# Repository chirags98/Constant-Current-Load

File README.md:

# Constant-Current-Load

This circuit uses an opamp and a mosfet as a voltage follower circuit. I can dial in any current I want and the circuit will adjust itself to draw that much current from the power supply regardless of the supply voltage. It can be 3 Volts, 5 Volts, 15 Volts whatever it might be and the load will adjust itself to draw the selected current.

This is a double sided board design which I got manufactured from a PCB prototyping firm in China.

I designed the circuit to have the following features

* To have a knob to vary the current from 1mA-2A
* Dissipate upto 30 watts of power
* Connect a supply upto 30 volts
* To have a LCD panel to show 
    * Current drawn
    * Voltage across the load
    * Power dissipated in the load
* Give warnings if power/current/voltage range are excedded
* Give the user the choice to run the circuit from the load supply thereby eliminating the need for an external power supply

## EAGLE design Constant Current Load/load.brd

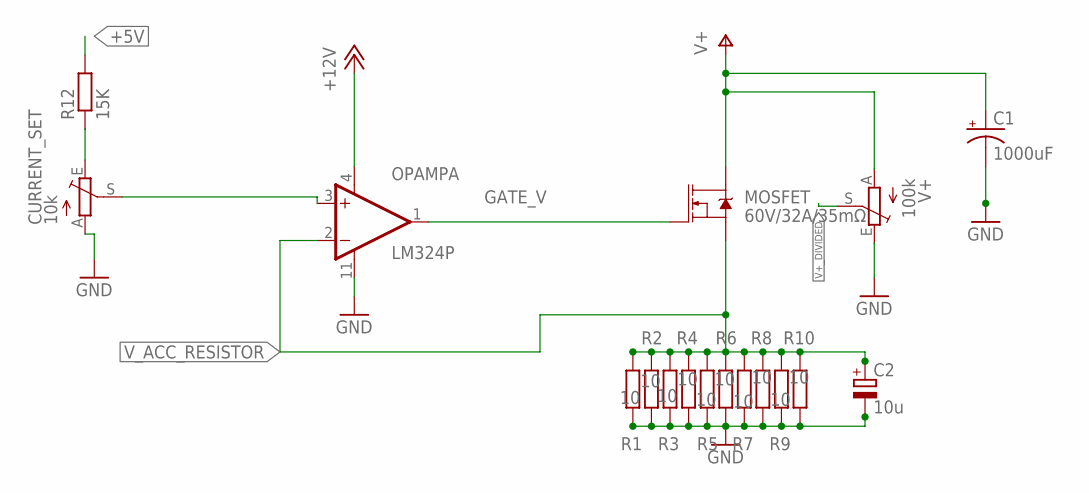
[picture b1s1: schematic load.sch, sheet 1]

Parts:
C1: 1000uF; CPOL-RADIAL-5MM-10MM
C2: 10u; E2,5-6E
CURRENT_SET: 10k; S64W
MOSFET: 60V/32A/35mΩ; TO220V
OPAMP: LM324P; DIL14
R1, R2, R3, R4, R5, R6, R7, R8, R9, R10: 10; 0207/12
R12: 15K; M0805
V+: 100k; S64W

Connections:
+5V: R12.2; also elsewhere on the board
+12V: OPAMP.4 (V+); also elsewhere on the board
GATE_V: MOSFET.1 (G), OPAMP.1 (OUT); also elsewhere on the board
GND: C1.-, C2.-, CURRENT_SET.A, OPAMP.11 (V-), R1.1, R2.1, R3.1, R4.1, R5.1, R6.1, R7.1, R8.1, R9.1, R10.1, V+.E; also elsewhere on the board
unnamed: CURRENT_SET.S, OPAMP.3 (+IN)
unnamed: CURRENT_SET.E, R12.1
V+: C1.+, MOSFET.2 (D), V+.A; also elsewhere on the board
V+_DIVIDED: V+.S; also elsewhere on the board
V_ACC_RESISTOR: C2.+, MOSFET.3 (S), OPAMP.2 (-IN), R1.2, R2.2, R3.2, R4.2, R5.2, R6.2, R7.2, R8.2, R9.2, R10.2; also elsewhere on the board

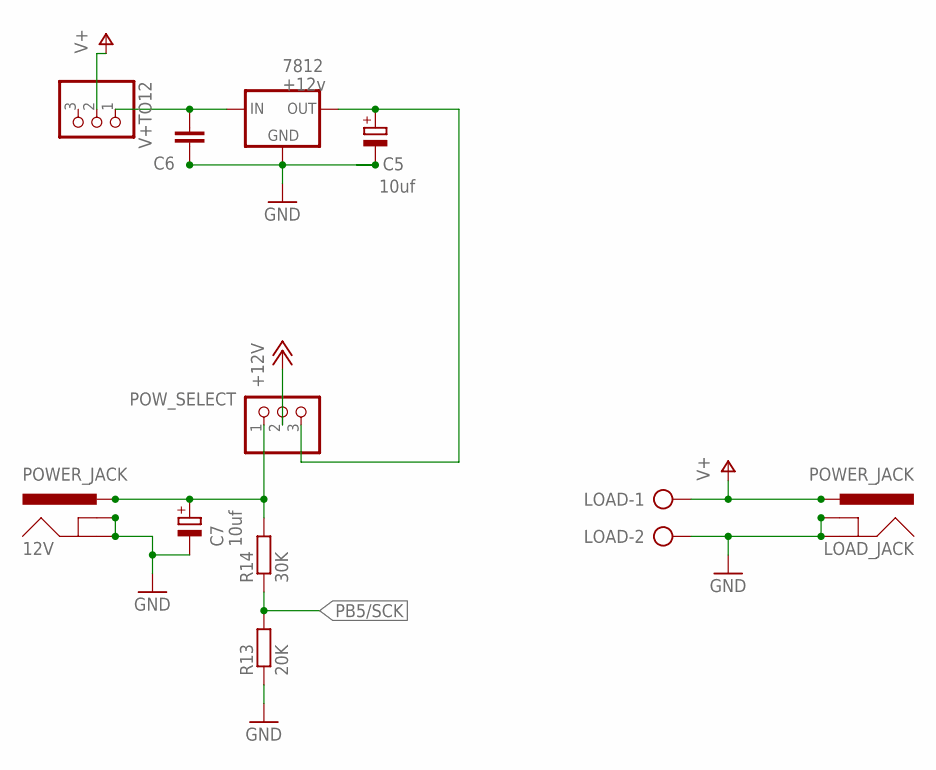
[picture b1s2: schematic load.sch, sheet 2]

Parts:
12V: POWER_JACK; POWER_JACK_PTH
7812: +12v; TO-252
C5, C7: 10uf; E2,5-6
C6: .1uF; C0805K
LOAD: AK500/2-H
LOAD_JACK: POWER_JACK; POWER_JACK_PTH
POW_SELECT: PINHD-1X3; 1X03
R13: 20K; M0805
R14: 30K; M0805
V+TO12: PINHD-1X3; 1X03

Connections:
12V_JACK_INPUT: 12V.PWR, C7.+, POW_SELECT.1, R14.2
12V_REG_O/P: 7812.2 (OUT), C5.+, POW_SELECT.3
+12V: POW_SELECT.2; also elsewhere on the board
GND: 12V.GND, 12V.GNDBREAK, 7812.3 (GND), C5.-, C6.2, C7.-, LOAD.2, LOAD_JACK.GND, LOAD_JACK.GNDBREAK, R13.1; also elsewhere on the board
unnamed: 7812.1 (IN), C6.1, V+TO12.1
PB5/SCK: R13.2, R14.1; also elsewhere on the board
V+: LOAD.1, LOAD_JACK.PWR, V+TO12.2; also elsewhere on the board

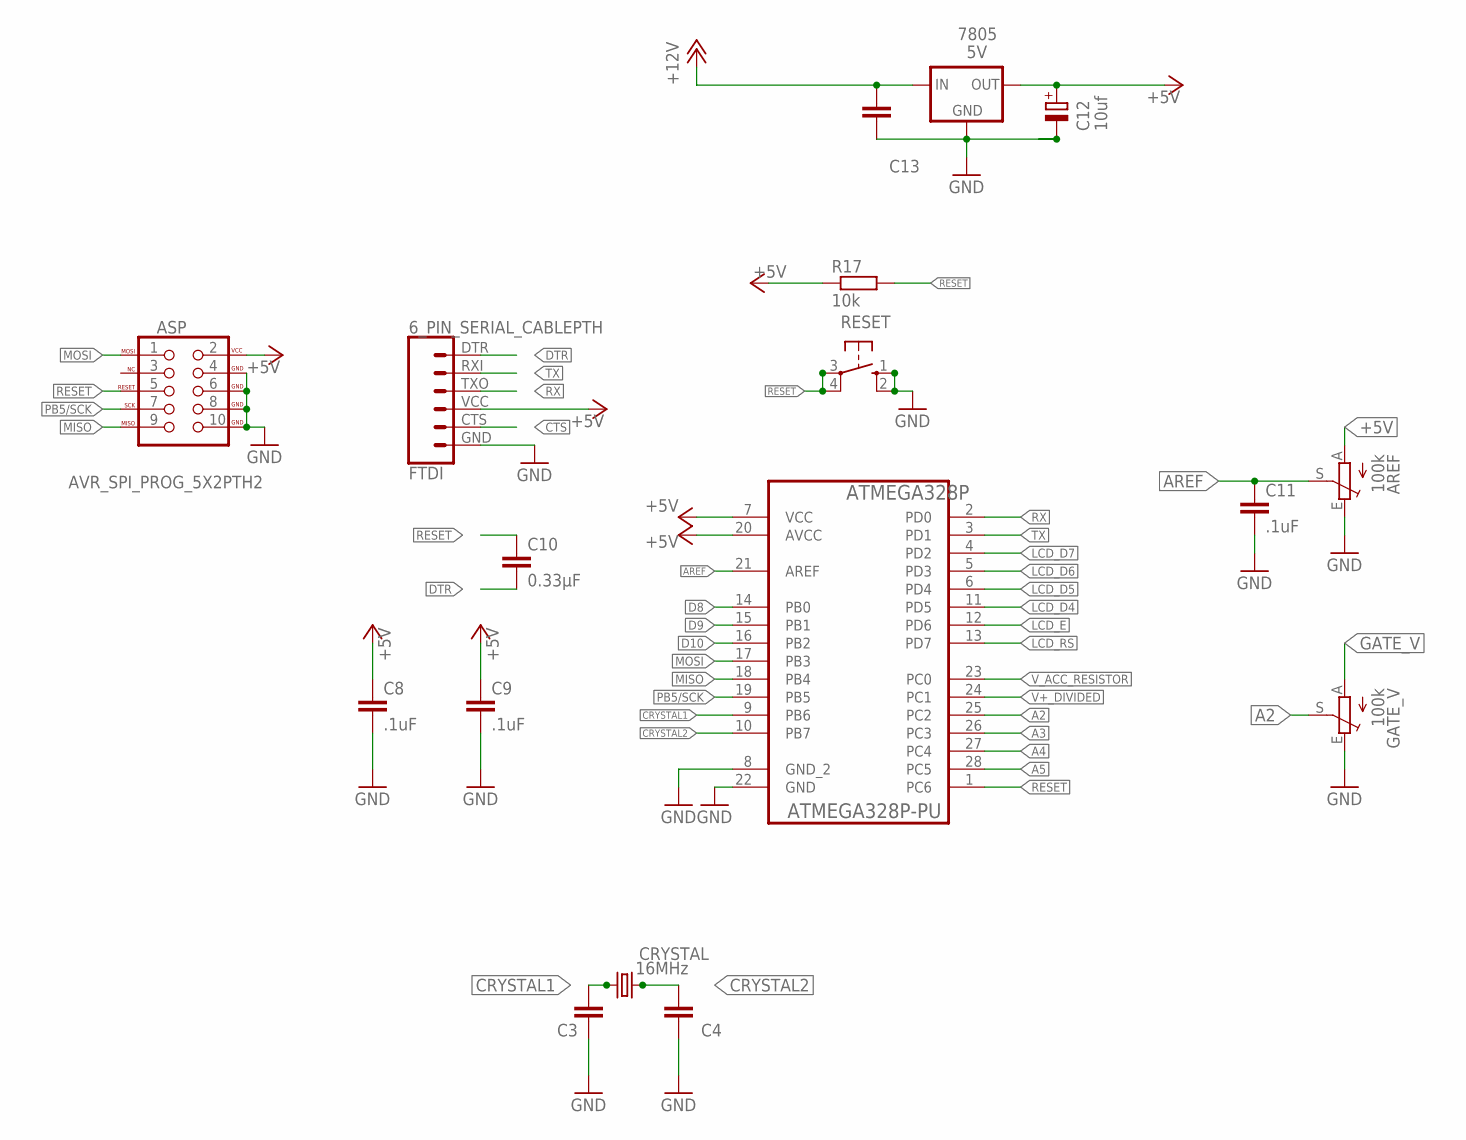
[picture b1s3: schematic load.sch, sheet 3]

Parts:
7805: 5V; TO-252
AREF: 100k; S64W
ASP: AVR_SPI_PROG_5X2PTH2; 2X5-SHROUDED
ATMEGA328P: ATMEGA328P-PU; DIP254P762X457-28
C3, C4: 22pF; C0805K
C8, C9, C11: .1uF; C0805K
C10: 0.33µF; C0805K
C12: 10uf; E2,5-6
C13: .1uf; C0805K
CRYSTAL: 16MHz; HC49U70
FTDI: 6_PIN_SERIAL_CABLEPTH; FTDI_BASIC
GATE_V: 100k; S64W
R17: 10k; M0805
RESET: 10-XX; B3F-10XX

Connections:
+5V: 7805.2 (OUT), AREF.A, ASP.2 (VCC), ATMEGA328P.7 (VCC), ATMEGA328P.20 (AVCC), C8.1, C9.1, C12.+, FTDI.VCC (4), R17.1; also elsewhere on the board
+12V: 7805.1 (IN), C13.1; also elsewhere on the board
A2: ATMEGA328P.25 (PC2), GATE_V.S
A3: ATMEGA328P.26 (PC3)
A4: ATMEGA328P.27 (PC4)
A5: ATMEGA328P.28 (PC5)
AREF: AREF.S, ATMEGA328P.21 (AREF), C11.1
CRYSTAL1: ATMEGA328P.9 (PB6), C3.2, CRYSTAL.1
CRYSTAL2: ATMEGA328P.10 (PB7), C4.2, CRYSTAL.2
CTS: FTDI.CTS (5)
D8: ATMEGA328P.14 (PB0)
D9: ATMEGA328P.15 (PB1)
D10: ATMEGA328P.16 (PB2)
DTR: C10.2, FTDI.DTR (1)
GATE_V: GATE_V.A; also elsewhere on the board
GND: 7805.3 (GND), AREF.E, ASP.4 (GND), ASP.6 (GND), ASP.8 (GND), ASP.10 (GND), ATMEGA328P.8 (GND_2), ATMEGA328P.22 (GND), C3.1, C4.1, C8.2, C9.2, C11.2, C12.-, C13.2, FTDI.GND (6), GATE_V.E, RESET.1 (S), RESET.2 (S1); also elsewhere on the board
LCD_D4: ATMEGA328P.11 (PD5); also elsewhere on the board
LCD_D5: ATMEGA328P.6 (PD4); also elsewhere on the board
LCD_D6: ATMEGA328P.5 (PD3); also elsewhere on the board
LCD_D7: ATMEGA328P.4 (PD2); also elsewhere on the board
LCD_E: ATMEGA328P.12 (PD6); also elsewhere on the board
LCD_RS: ATMEGA328P.13 (PD7); also elsewhere on the board
MISO: ASP.9 (MISO), ATMEGA328P.18 (PB4)
MOSI: ASP.1 (MOSI), ATMEGA328P.17 (PB3)
PB5/SCK: ASP.7 (SCK), ATMEGA328P.19 (PB5); also elsewhere on the board
RESET: ASP.5 (RESET), ATMEGA328P.1 (PC6), C10.1, R17.2, RESET.3, RESET.4 (P1)
RX: ATMEGA328P.2 (PD0), FTDI.TXO (3)
TX: ATMEGA328P.3 (PD1), FTDI.RXI (2)
V+_DIVIDED: ATMEGA328P.24 (PC1); also elsewhere on the board
V_ACC_RESISTOR: ATMEGA328P.23 (PC0); also elsewhere on the board

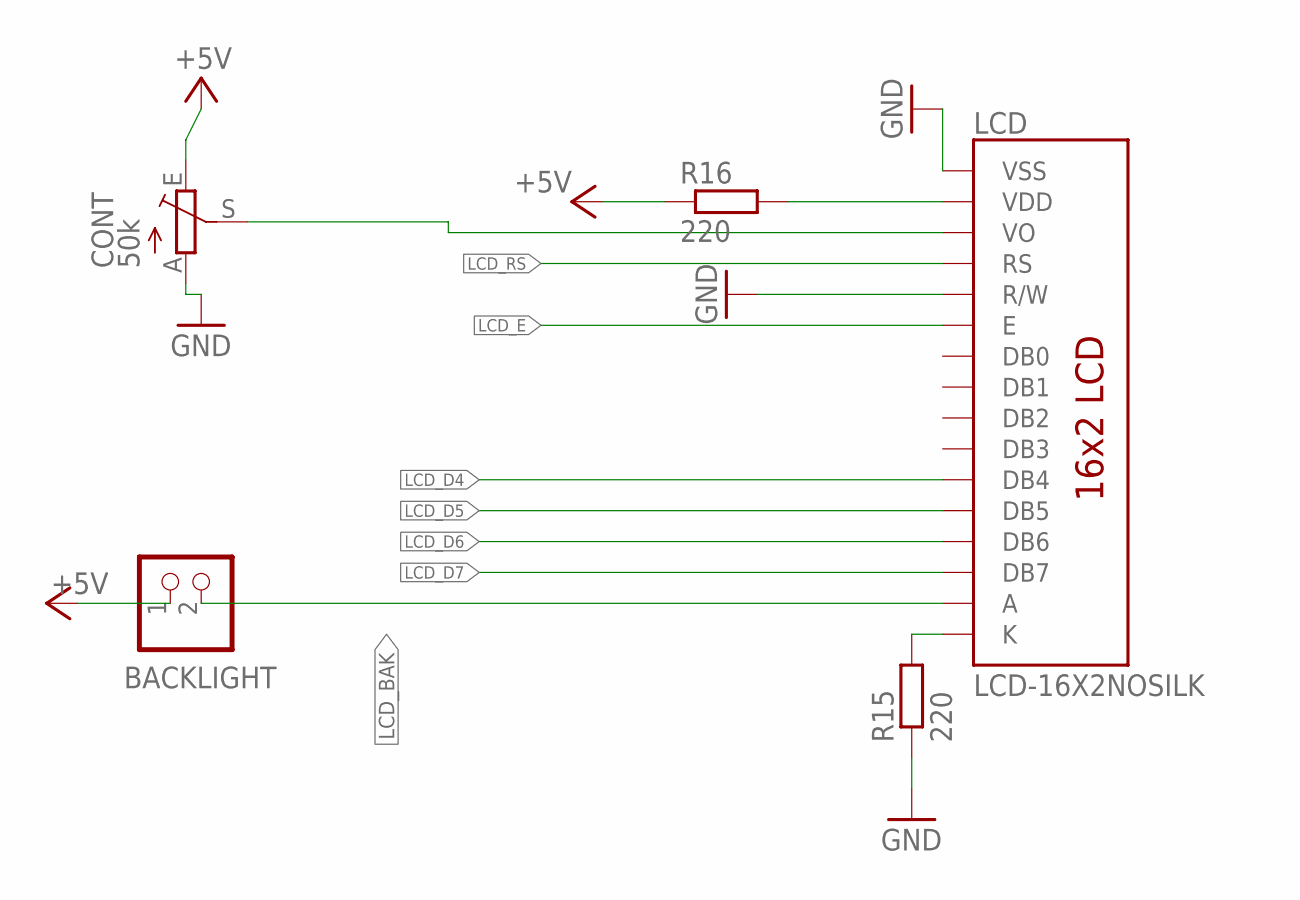
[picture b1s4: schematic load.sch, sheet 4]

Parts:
BACKLIGHT: PINHD-1X2; 1X02
CONT: 50k; S64W
LCD: LCD-16X2NOSILK; LCD-16X2_NOSILK
R15, R16: 220; M0805

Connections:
+5V: BACKLIGHT.1, CONT.E, R16.1; also elsewhere on the board
GND: CONT.A, LCD.1 (VSS), LCD.5 (R/W), R15.1; also elsewhere on the board
LCD_BAK: BACKLIGHT.2, LCD.15 (A)
LCD_D4: LCD.11 (DB4); also elsewhere on the board
LCD_D5: LCD.12 (DB5); also elsewhere on the board
LCD_D6: LCD.13 (DB6); also elsewhere on the board
LCD_D7: LCD.14 (DB7); also elsewhere on the board
LCD_E: LCD.6 (E); also elsewhere on the board
LCD_RS: LCD.4 (RS); also elsewhere on the board
unnamed: CONT.S, LCD.3 (VO)
unnamed: LCD.2 (VDD), R16.2
unnamed: LCD.16 (K), R15.2

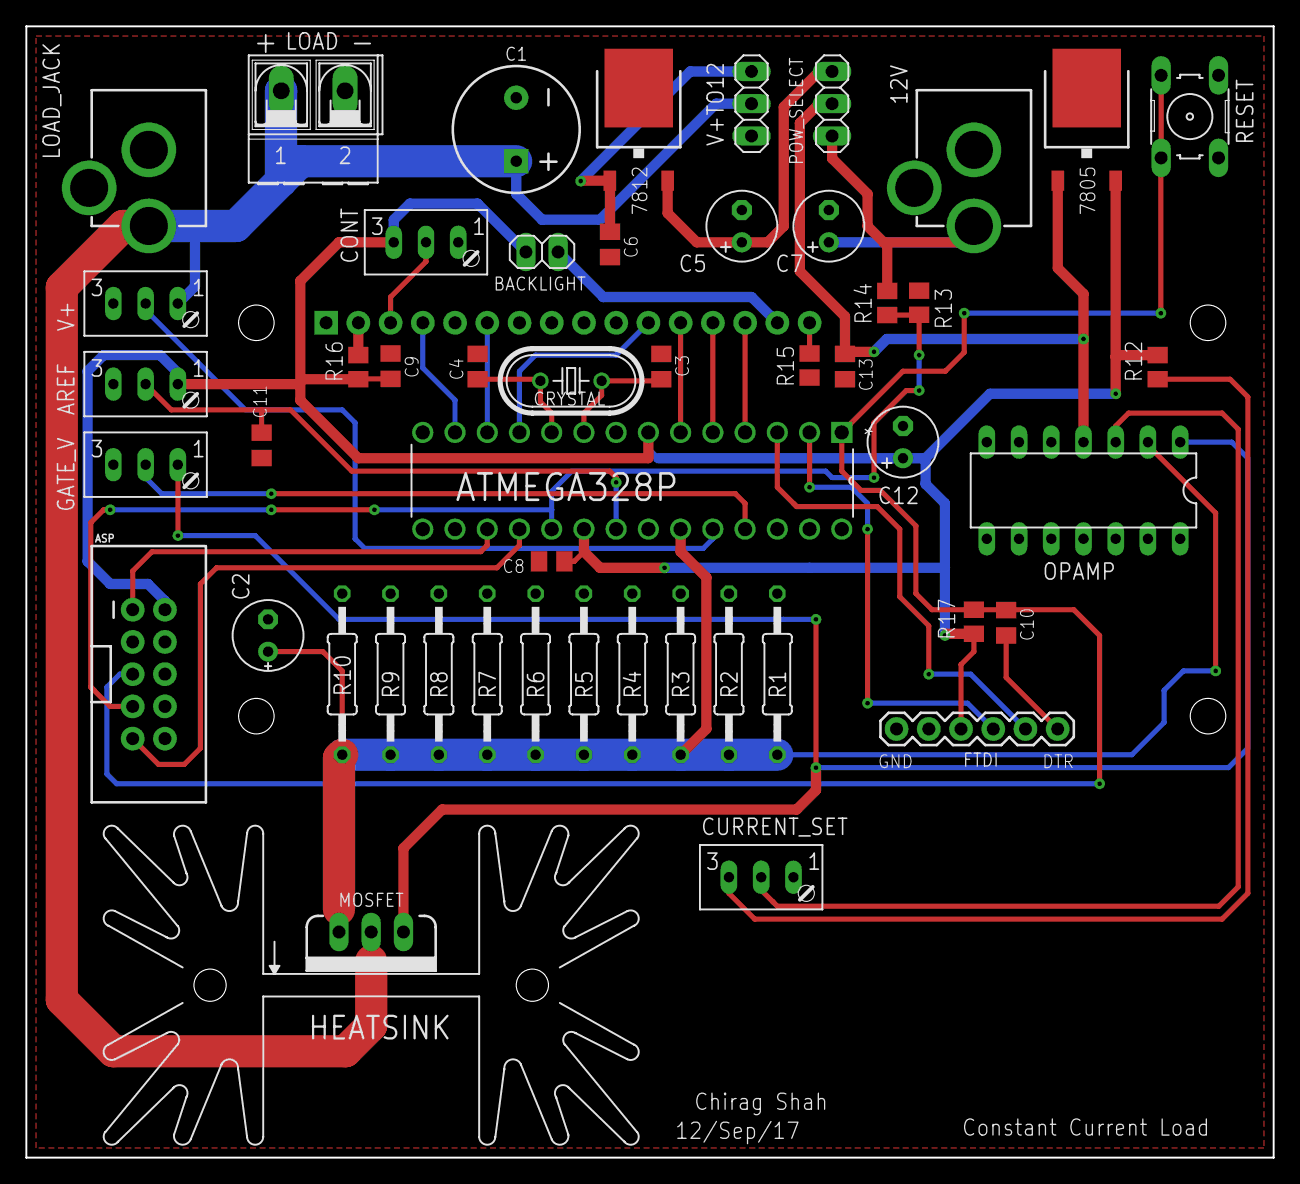
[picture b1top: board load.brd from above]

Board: 2 copper layers, 98.3 x 89.2 mm, 51 parts (0 on the bottom side), 33 nets.

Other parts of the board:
HEATSINK: SK129-HOLE

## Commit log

2017-07-22 Pushing latest version
2017-08-29 Starting work on double sided board
2017-09-02 Replaced through hole with smd
2017-09-02 Routed the pcb v1
2017-09-08 Still working
2017-09-11 Complete I guess
2017-09-12 Before moving HS and Pot
2017-09-12 Final
2018-02-16 Updated the README

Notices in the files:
parts and their libraries:
SparkFun-Connectors: Licensing: Creative Commons ShareAlike 4.0 International - https://creativecommons.org/licenses/by-sa/4.0
